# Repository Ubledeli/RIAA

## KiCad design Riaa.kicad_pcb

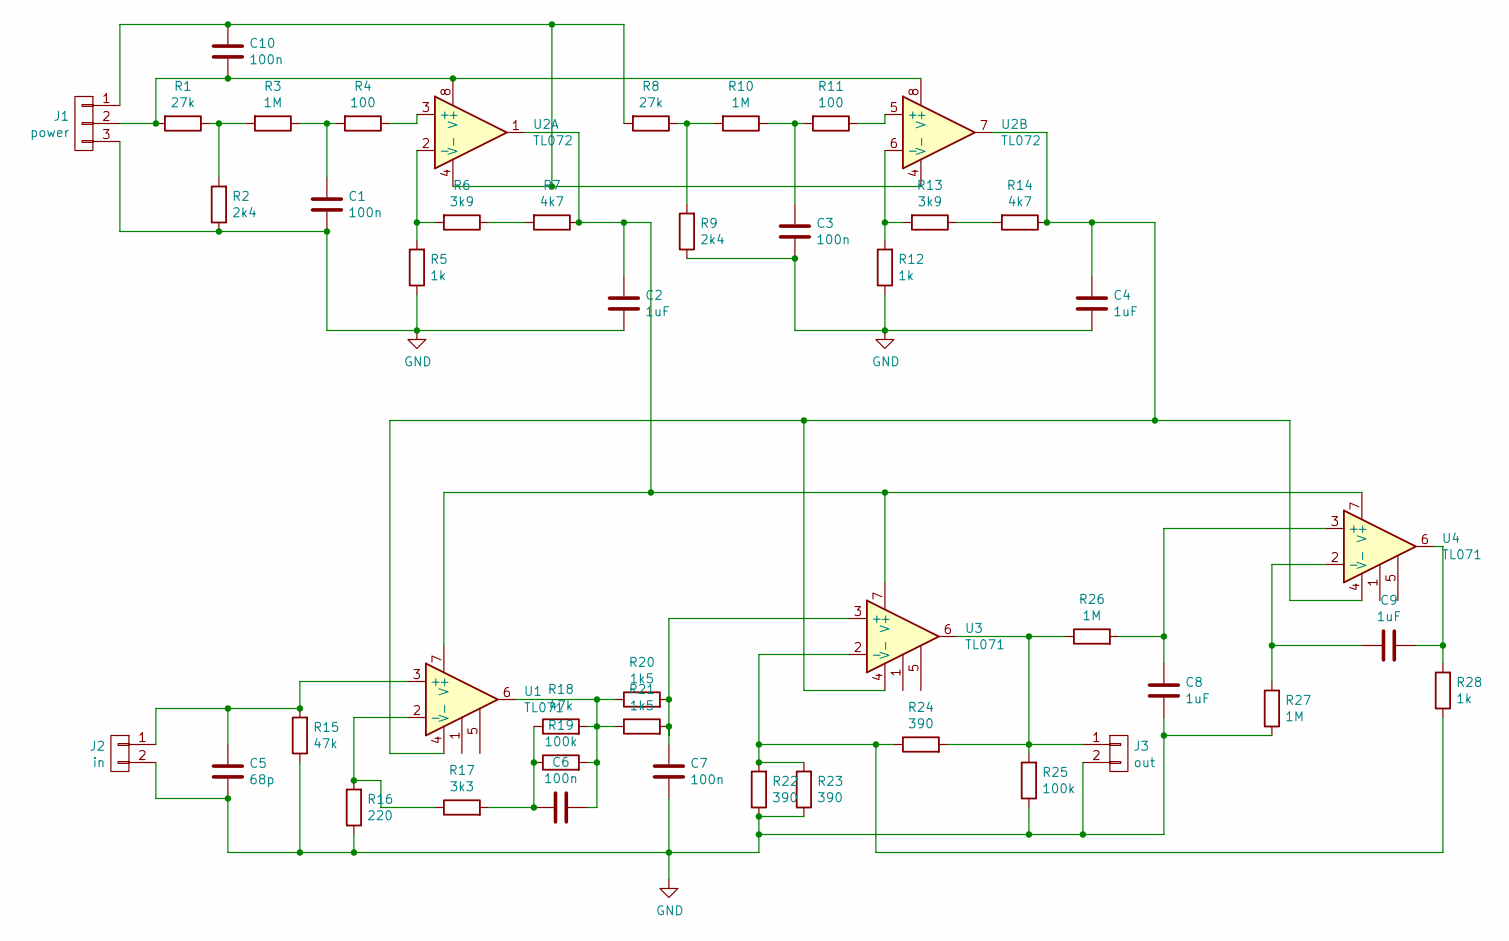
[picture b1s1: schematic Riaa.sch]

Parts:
C1, C3, C6, C7, C10: 100n; C_Rect_L7.2mm_W2.5mm_P5.00mm_FKS2_FKP2_MKS2_MKP2
C2, C4, C8, C9: 1uF; C_Rect_L7.2mm_W5.5mm_P5.00mm_FKS2_FKP2_MKS2_MKP2
C5: 68p; C_Rect_L7.2mm_W2.5mm_P5.00mm_FKS2_FKP2_MKS2_MKP2
J1: power; PINHEAD1-3
J2: in; PINHEAD1-2
J3: out; PINHEAD1-2
R1, R8: 27k; R_Axial_DIN0207_L6.3mm_D2.5mm_P7.62mm_Horizontal
R2, R9: 2k4; R_Axial_DIN0207_L6.3mm_D2.5mm_P7.62mm_Horizontal
R3, R10, R26, R27: 1M; R_Axial_DIN0207_L6.3mm_D2.5mm_P7.62mm_Horizontal
R4, R11: 100; R_Axial_DIN0207_L6.3mm_D2.5mm_P7.62mm_Horizontal
R5, R12, R28: 1k; R_Axial_DIN0207_L6.3mm_D2.5mm_P7.62mm_Horizontal
R6, R13: 3k9; R_Axial_DIN0207_L6.3mm_D2.5mm_P7.62mm_Horizontal
R7, R14: 4k7; R_Axial_DIN0207_L6.3mm_D2.5mm_P7.62mm_Horizontal
R15, R18: 47k; R_Axial_DIN0207_L6.3mm_D2.5mm_P7.62mm_Horizontal
R16: 220; R_Axial_DIN0207_L6.3mm_D2.5mm_P7.62mm_Horizontal
R17: 3k3; R_Axial_DIN0207_L6.3mm_D2.5mm_P7.62mm_Horizontal
R19, R25: 100k; R_Axial_DIN0207_L6.3mm_D2.5mm_P7.62mm_Horizontal
R20, R21: 1k5; R_Axial_DIN0207_L6.3mm_D2.5mm_P7.62mm_Horizontal
R22, R23, R24: 390; R_Axial_DIN0207_L6.3mm_D2.5mm_P7.62mm_Horizontal
U1, U3, U4: TL071; DIP-8_W7.62mm
U2: TL072; DIP-8_W7.62mm

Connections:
GND: C1.2, C2.2, C3.2, C4.2, C5.2, C7.2, C8.2, J1.3, J2.2, J3.2, R2.1, R5.1, R9.1, R12.1, R15.1, R16.1, R22.1, R23.1, R25.1, R27.1
unnamed: C1.1, R3.1, R4.2
unnamed: C2.1, R7.1, U1.7 (V+), U2.1, U3.7 (V+), U4.7 (V+)
unnamed: C3.1, R10.1, R11.2
unnamed: C4.1, R14.1, U1.4 (V-), U2.7, U3.4 (V-), U4.4 (V-)
unnamed: C5.1, J2.1, R15.2, U1.3 (+)
unnamed: C6.1, R18.2, R19.2, R20.1, R21.1, U1.6
unnamed: C6.2, R17.2, R18.1, R19.1
unnamed: C7.1, R20.2, R21.2, U3.3 (+)
unnamed: C8.1, R26.2, U4.3 (+)
unnamed: C9.1, R28.2, U4.6
unnamed: C9.2, R27.2, U4.2 (-)
unnamed: C10.1, J1.1, R8.2, U2.4 (V-)
unnamed: C10.2, J1.2, R1.2, U2.8 (V+)
unnamed: J3.1, R24.2, R25.2, R26.1, U3.6
unnamed: R1.1, R2.2, R3.2
unnamed: R4.1, U2.3 (+)
unnamed: R5.2, R6.2, U2.2 (-)
unnamed: R6.1, R7.2
unnamed: R8.1, R9.2, R10.2
unnamed: R11.1, U2.5 (+)
unnamed: R12.2, R13.2, U2.6 (-)
unnamed: R13.1, R14.2
unnamed: R16.2, R17.1, U1.2 (-)
unnamed: R22.2, R23.2, R24.1, R28.1, U3.2 (-)

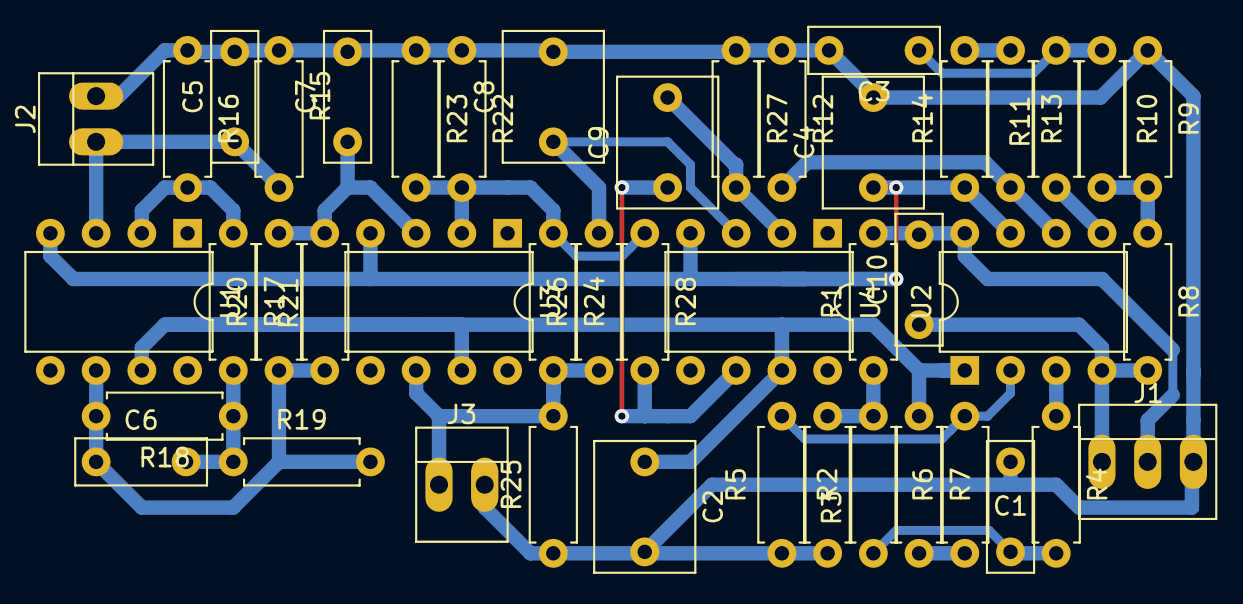
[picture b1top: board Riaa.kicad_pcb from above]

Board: 2 copper layers, 45 parts (0 on the bottom side), 25 nets.

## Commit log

2017-05-05 schematic
2017-05-05 component values
2017-05-07 pads
2017-05-08 layout
2017-05-14 decoupling
2017-05-17 routing
2017-09-27 65x30mm
